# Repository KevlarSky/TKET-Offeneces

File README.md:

# TKET-Offeneces
A series of half thought through projects for the TKET Group

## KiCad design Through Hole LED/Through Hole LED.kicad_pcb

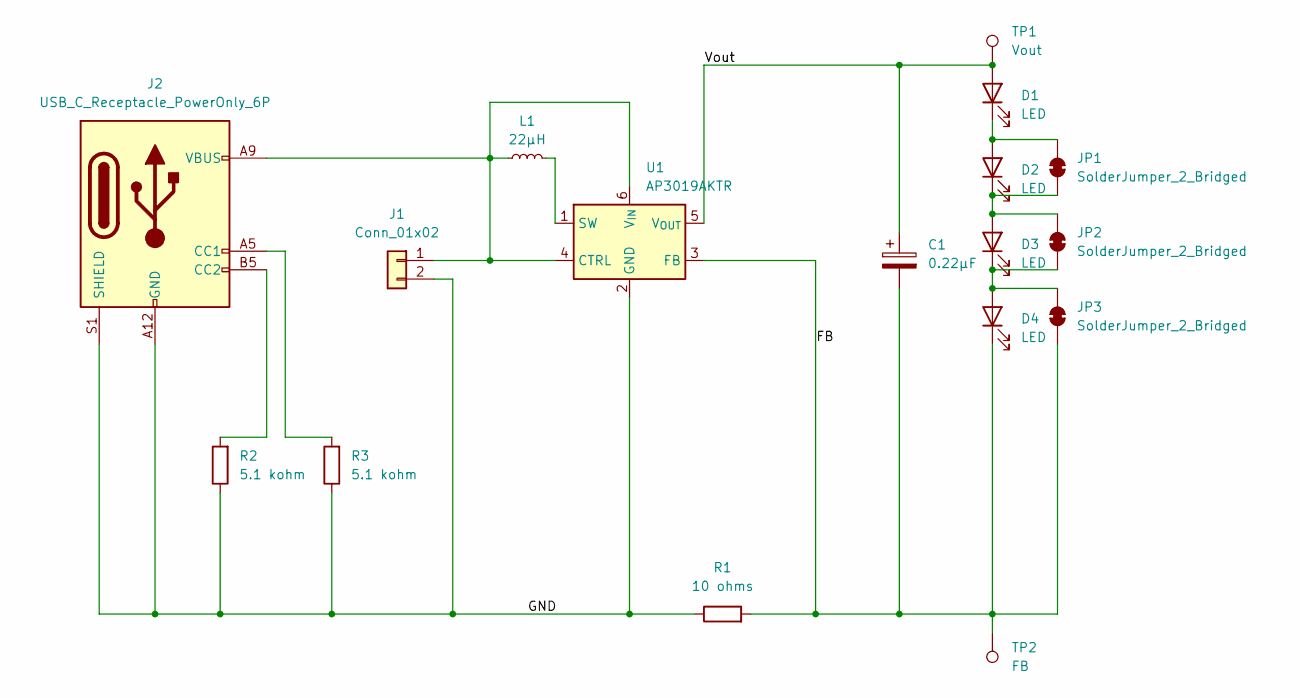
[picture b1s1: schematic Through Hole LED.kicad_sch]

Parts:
C1: 0.22µF; CP_Radial_D5.0mm_P2.00mm
D1, D2, D3, D4: LED; LED_D3.0mm
J1: Conn_01x02; PinHeader_1x02_P2.54mm_Vertical
J2: USB_C_Receptacle_PowerOnly_6P; USB_C_Receptacle_GCT_USB4125-xx-x_6P_TopMnt_Horizontal
JP1, JP2, JP3: SolderJumper_2_Bridged; SolderJumper-2_P1.3mm_Bridged_RoundedPad1.0x1.5mm
L1: 22µH; L_Radial_D10.5mm_P5.00mm_Abacron_AISR-01
R1: 10 ohms; R_Axial_DIN0207_L6.3mm_D2.5mm_P10.16mm_Horizontal
R2, R3: 5.1 kohm; R_Axial_DIN0207_L6.3mm_D2.5mm_P10.16mm_Horizontal
TP1: Vout; TestPoint_Pad_D2.0mm
TP2: FB; TestPoint_Pad_D2.0mm
U1: AP3019AKTR; SOT-23-6_Handsoldering

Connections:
/FB: C1.2, D4.1 (K), JP3.1 (A), R1.2, TP2.1, U1.3 (FB)
/GND: J1.2, J2.A12 (GND), J2.B12 (GND), J2.S1 (SHIELD), R1.1, R2.1, R3.1, U1.2 (GND)
/Vout: C1.1, D1.2 (A), TP1.1, U1.5 (V_{OUT})
unnamed: D1.1 (K), D2.2 (A), JP1.2 (B)
unnamed: D2.1 (K), D3.2 (A), JP1.1 (A), JP2.2 (B)
unnamed: D3.1 (K), D4.2 (A), JP2.1 (A), JP3.2 (B)
unnamed: J1.1, J2.A9 (VBUS), J2.B9 (VBUS), L1.1, U1.4 (CTRL), U1.6 (V_{IN})
unnamed: J2.A5 (CC1), R3.2
unnamed: J2.B5 (CC2), R2.2
unnamed: L1.2, U1.1 (SW)

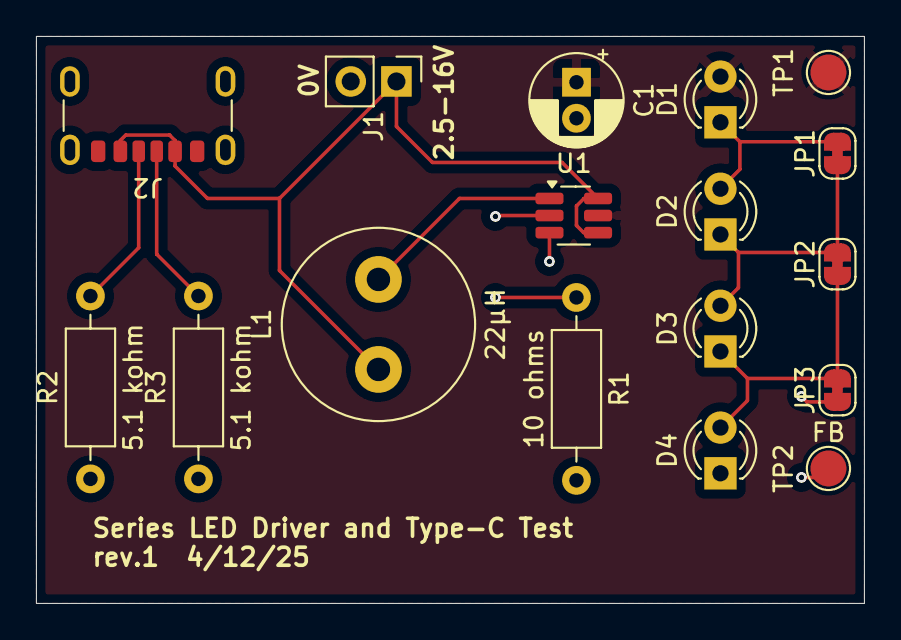
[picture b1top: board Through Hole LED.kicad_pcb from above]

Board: 2 copper layers, 46.0 x 31.5 mm, 17 parts (0 on the bottom side), 10 nets.

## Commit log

2024-03-31 Update Garge Door Controller.md
    Additions after looking at hardware
2024-03-31 Picture of Motor
2024-03-31 Garage Buttons
